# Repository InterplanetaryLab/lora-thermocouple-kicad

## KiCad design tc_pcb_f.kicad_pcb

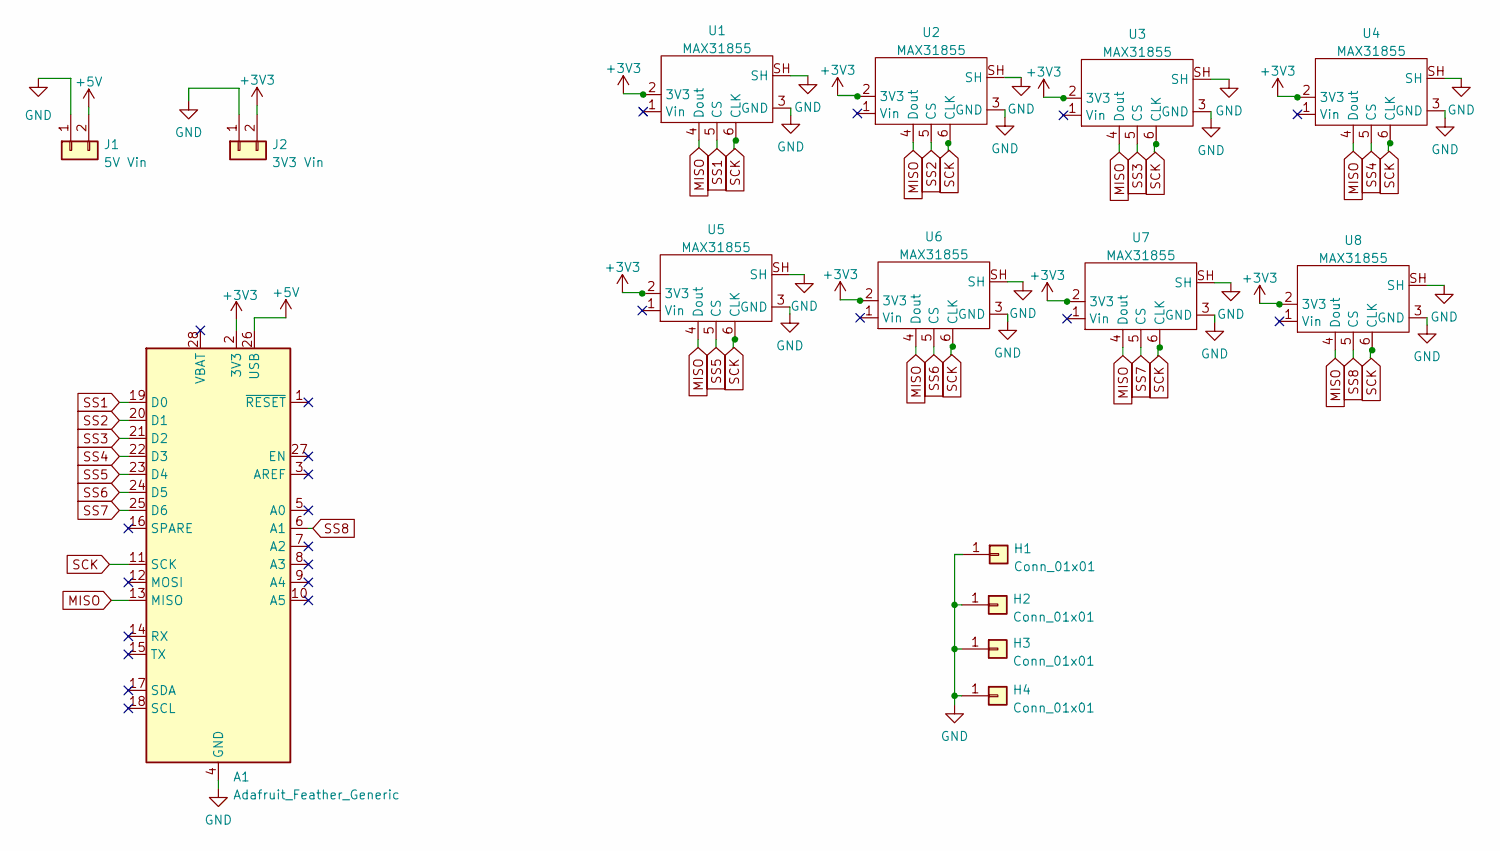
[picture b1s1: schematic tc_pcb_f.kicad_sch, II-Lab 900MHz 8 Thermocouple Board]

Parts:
A1: Adafruit_Feather_Generic; Adafruit_Feather
H1, H2, H3, H4: Conn_01x01; 3mm_hole
J1: 5V Vin; dupont2x1
J2: 3V3 Vin; dupont2x1
U1, U2, U3, U4, U5, U6, U7, U8: MAX31855; adafruit_max31855

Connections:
+3V3: A1.2 (3V3), J2.2, U1.2 (3V3), U2.2 (3V3), U3.2 (3V3), U4.2 (3V3), U5.2 (3V3), U6.2 (3V3), U7.2 (3V3), U8.2 (3V3)
+5V: A1.26 (USB), J1.2
GND: A1.4 (GND), H1.1, H2.1, H3.1, H4.1, J1.1, J2.1, U1.3 (GND), U1.SH, U2.3 (GND), U2.SH, U3.3 (GND), U3.SH, U4.3 (GND), U4.SH, U5.3 (GND), U5.SH, U6.3 (GND), U6.SH, U7.3 (GND), U7.SH, U8.3 (GND), U8.SH
MISO: A1.13 (MISO), U1.4 (Dout), U2.4 (Dout), U3.4 (Dout), U4.4 (Dout), U5.4 (Dout), U6.4 (Dout), U7.4 (Dout), U8.4 (Dout)
SCK: A1.11 (SCK), U1.6 (CLK), U2.6 (CLK), U3.6 (CLK), U4.6 (CLK), U5.6 (CLK), U6.6 (CLK), U7.6 (CLK), U8.6 (CLK)
SS1: A1.19 (D0), U1.5 (CS)
SS2: A1.20 (D1), U2.5 (CS)
SS3: A1.21 (D2), U3.5 (CS)
SS4: A1.22 (D3), U4.5 (CS)
SS5: A1.23 (D4), U5.5 (CS)
SS6: A1.24 (D5), U6.5 (CS)
SS7: A1.25 (D6), U7.5 (CS)
SS8: A1.6 (A1), U8.5 (CS)

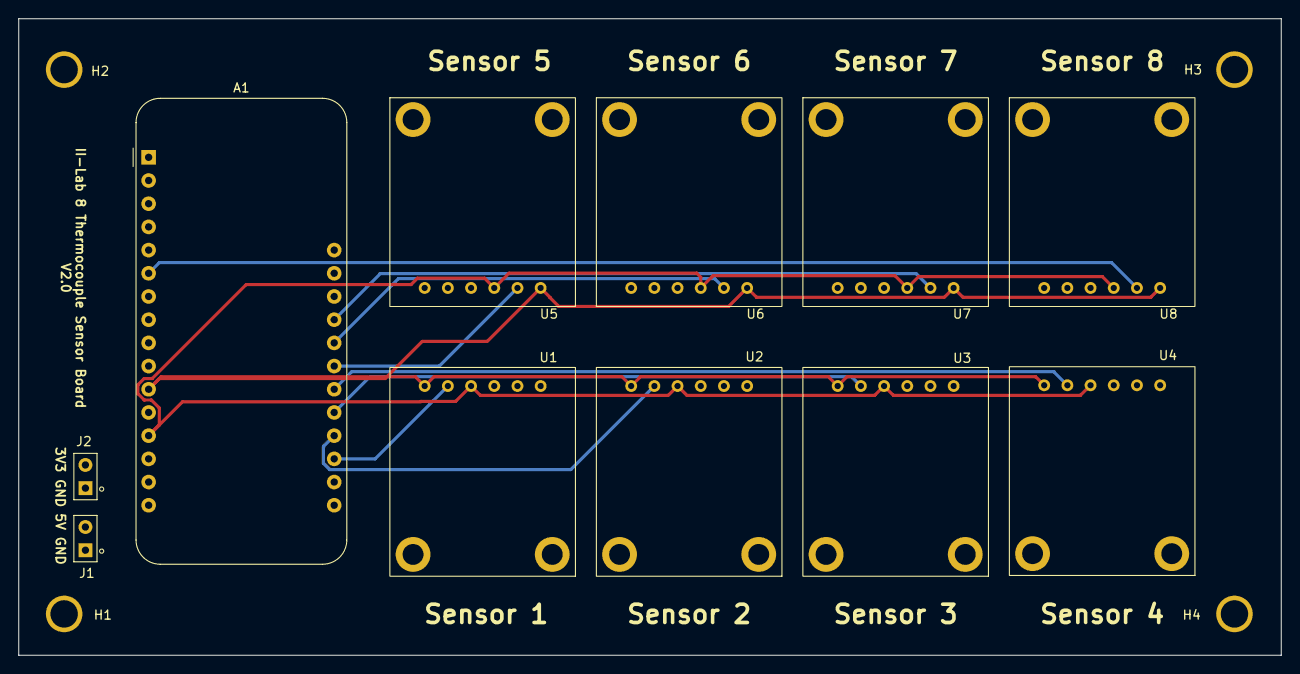
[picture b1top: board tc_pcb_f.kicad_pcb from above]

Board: 4 copper layers, 138.2 x 69.7 mm, 15 parts (0 on the bottom side), 13 nets.

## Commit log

2022-06-06 inital commit of 4 amplifier variant
2022-06-07 finished layout for 8 sensor board
2022-06-07 commiting updates
2022-08-26 fixing some autosaves
